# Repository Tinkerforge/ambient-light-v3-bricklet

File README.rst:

Ambient Light Bricklet 3.0
==========================

This repository contains the firmware source code and the hardware design
files. The documentation generator configs can be found at
https://github.com/Tinkerforge/generators

Repository Content
------------------

software/:
 * examples/: Examples for all supported languages
 * build/: Compiled files
 * src/: Source code of firmware
 * Makefile: Makefile to build project

hardware/:
 * Contains KiCad project files and additionally schematics as PDF

datasheets/:
 * Contains datasheets for sensors and complex ICs that are used

Hardware
--------

The hardware is designed with the open source EDA Suite KiCad
(http://www.kicad.org). Before you are able to open the files,
you have to install the Tinkerforge kicad-libraries
(https://github.com/Tinkerforge/kicad-libraries). You can either clone
them directly in hardware/ or clone them in a separate folder and
symlink them into hardware/
(ln -s kicad_path/kicad-libraries project_path/hardware). After that you
can open the .pro file in hardware/ with KiCad and from there view and
modify the schematics and the PCB layout.

Software
--------

If you want to do your own Brick/Bricklet firmware development we highly
recommend that you use our build environment setup script and read the
tutorial (https://www.tinkerforge.com/en/doc/Tutorials/Tutorial_Build_Environment/Tutorial.html).

To compile the C code we recommend you to install the newest GNU Arm Embedded
Toolchain (https://launchpad.net/gcc-arm-embedded/+download).
You also need to install bricklib2 (https://github.com/Tinkerforge/bricklib2).

You can either clone it directly in software/src/ or clone it in a
separate folder and symlink it into software/src/
(ln -s bricklib_path/bricklib2 project_path/software/src/). Finally make sure to
have CMake installed (http://www.cmake.org/cmake/resources/software.html).

After that you can build the firmware by invoking make in software/.
The firmware (.zbin) can then be found in software/build/ and uploaded
with brickv (click button "Flashing" on start screen).

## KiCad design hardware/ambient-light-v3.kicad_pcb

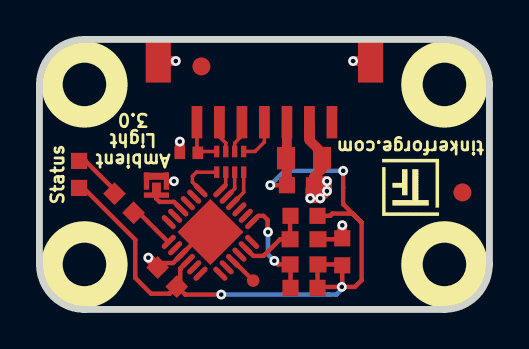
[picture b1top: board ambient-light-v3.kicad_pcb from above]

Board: 2 copper layers, 25.0 x 15.0 mm, 23 parts (2 on the bottom side), 16 nets.

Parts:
C1: 220pF; C0402F
C2, C5: 100nF; C0603F
C3: 10uF; C0805
C4: 1uF; C0603F
D1: blue; D0603F
Fiducial_Mark: VAL**; Fiducial_Mark
Fiducial_Mark#2: VAL**; Fiducial_Mark
P1: CON-SENSOR2
P2: DEBUG; DEBUG_PAD
P3: BOOT; SolderJumper
R1, R2: 2k2; R0603F
R3: 1k; R0603F
RP1: 82; 4X0402
U1: XMC1100; QFN24-4x4mm-0.5mm
U2: LTR-329ALS
U3, U4, U5, U6: DRILL; DRILL_NP
VAL: CE_5mm
VAL#2: WEEE_7mm

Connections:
GND: C1.2, C2.1, C3.2, C4.2, C5.2, P1.2, P1.EP, P3.1, U1.9, U1.EXP, U2.2
unnamed: C1.1, P1.7, RP1.4
unnamed: D1.2, R3.2
unnamed: P1.4, RP1.1
unnamed: P1.5, RP1.2
unnamed: P1.6, RP1.3
unnamed: P2.1, U1.15
unnamed: P3.2, U1.4
unnamed: R3.1, U1.7
S-CLK: RP1.7, U1.23
S-CS: RP1.8, U1.22
S-MISO: RP1.5, U1.1
S-MOSI: RP1.6, U1.24
SCL: R2.2, U1.19, U2.4
SDA: R1.2, U1.17, U2.3
VCC: C2.2, C3.1, C4.1, C5.1, D1.1, P1.3, R1.1, R2.1, U1.10, U2.1

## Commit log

2018-06-22 Add datasheets
2018-06-22 Add schematic
2018-06-22 Add layout
2018-06-22 Rename files to correct version
2018-06-22 Add logos
2018-06-28 Add .gitignore
2018-06-28 Fix readme
2018-07-11 Fix origin
2018-07-27 Add auto-generated stub firmware
2018-10-24 Add LTR329 driver and API implementation
2018-11-07 rust: Accept host names for ip connection, fix naming inconsistencies
2018-11-07 rust: Rename callback receivers.
2018-11-09 specify processor as xmc1100
2018-12-14 Add go examples.
2018-12-14 go: Fix printf parameters.
2018-12-18 go: Change import path.
2018-12-18 go: Change import path again.
2018-12-19 go: Remove temporary file.
2018-12-20 Add examples.
2018-12-20 rust: Reformat examples.
2019-01-24 mqtt: Add examples.
2019-01-24 mqtt: Fix example header.
2019-01-24 mqtt: Remove executable bit in example permissions.
2019-01-24 go: Minor example fixes.
2019-01-24 mqtt: Minor example fixes.
2019-01-28 Make sure bootloader fix is applied
2019-01-28 Remove obsolete TODO
2019-01-28 Add rev for initial release
2019-01-29 add sym table
2019-01-29 add schematic as pdf
2019-01-29 add 3d data
2019-01-29 change 3d data
2019-01-29 Remove in-development marker
2019-03-28 mqtt: Fix whitespace.
2019-05-16 Add LabVIEW examples
2019-05-29 Increase version for new release (changes in bricklib2)
2019-05-29 Add rev to changelog
2019-08-22 c: Adapt to bindings changes
2020-01-13 examples: Use python3 input instead of python2 raw_input.
2020-01-13 examples: mqtt: Remove trailing whitespace.
2020-08-19 Add uc examples.
2020-08-25 uc: Fix whitespace
2020-08-27 uc: Fix warnings.
2020-09-02 uc: Add example driver note.
2020-10-16 uc: Fix divisor type.
2021-10-25 Update KiCad link
    https://www.kicad.org/blog/2021/10/Avoid-links-to-former-kicad-domain/
2022-04-19 examples: uc: Rename TF_HalContext to TF_HAL.
2022-04-27 uc: Adapt to bindings changes
2022-07-06 Add license files.
2025-03-13 Improve robustness of i2c communication
2025-03-13 Add rev for firmware version 2.0.2
2025-10-01 Increase required cmake version

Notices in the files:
hardware/ambient-light-v3.kicad_pcb:
Licensed under CERN OHL v.1.1
Copyright (©) 2015, B.Nordmeyer
Copyright Tinkerforge GmbH 2015.
This documentation describes Open Hardware and is licensed under the
CERN OHL v. 1.1.
